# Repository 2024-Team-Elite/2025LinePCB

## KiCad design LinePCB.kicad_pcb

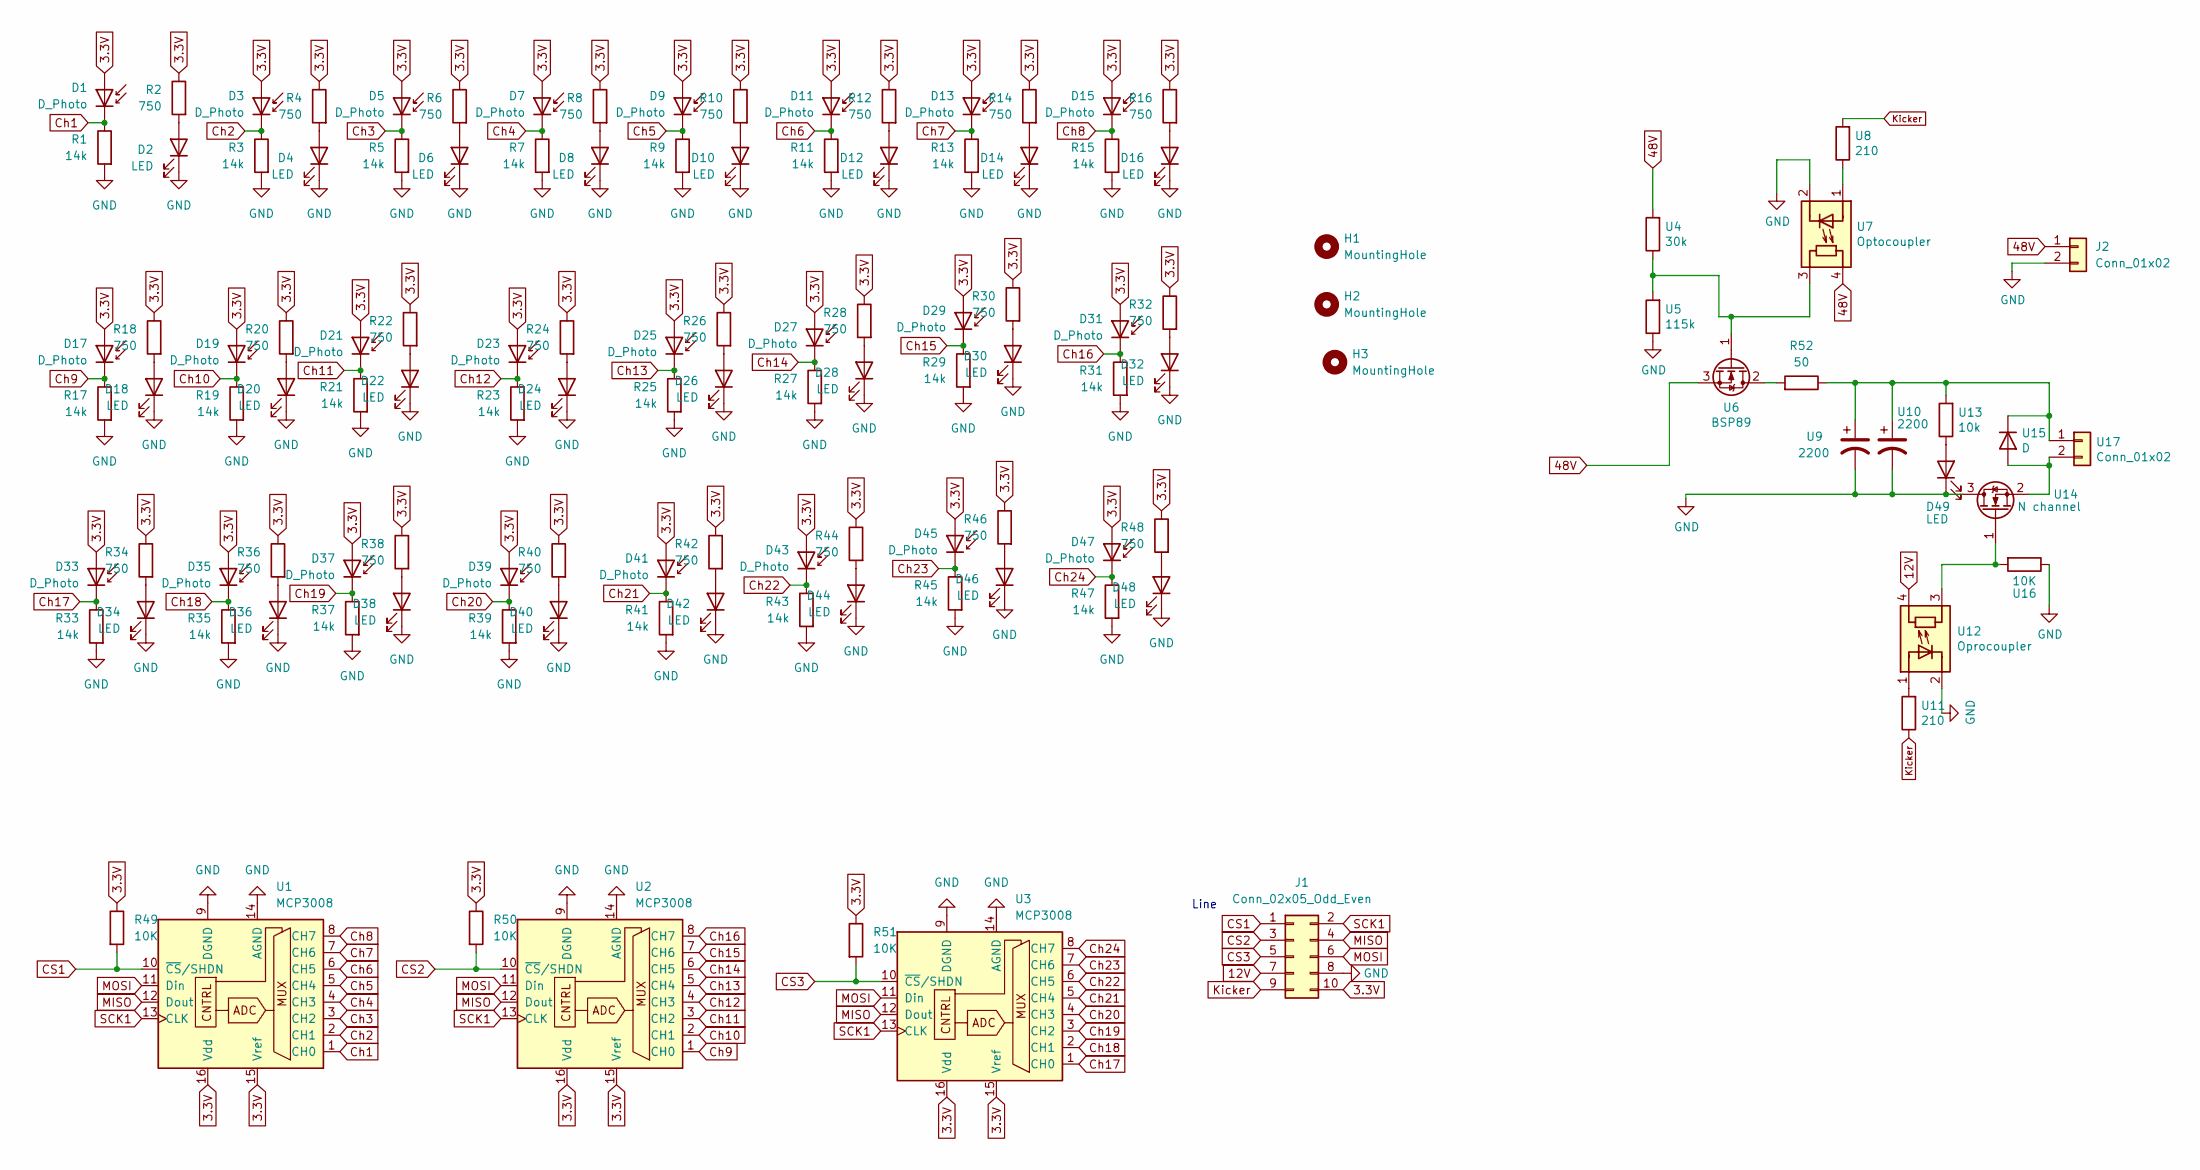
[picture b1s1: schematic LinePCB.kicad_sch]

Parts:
D1, D3, D5, D7, D9, D11, D13, D15, D17, D19, D21, D23, D25, D27, D29, D31, D33, D35, D37, D39, D41, D43, D45, D47: D_Photo; D_0805_2012Metric_Pad1.15x1.40mm_HandSolder
D2, D4, D6, D8, D10, D12, D14, D16, D18, D20, D22, D24, D26, D28, D30, D32, D34, D36, D38, D40, D42, D44, D46, D48, D49: LED; LED_0805_2012Metric_Pad1.15x1.40mm_HandSolder
H1, H2, H3: MountingHole; MountingHole_3.2mm_M3_DIN965_Pad
J1: Conn_02x05_Odd_Even; IDC-Header_2x05_P2.54mm_Vertical
J2: Conn_01x02; JST_XH_B2B-XH-A_1x02_P2.50mm_Vertical
R1, R3, R5, R7, R9, R11, R13, R15, R17, R19, R21, R23, R25, R27, R29, R31, R33, R35, R37, R39, R41, R43, R45, R47: 14k; R_0805_2012Metric_Pad1.20x1.40mm_HandSolder
R2, R4, R6, R8, R10, R12, R14, R16, R18, R20, R22, R24, R26, R28, R30, R32, R34, R36, R38, R40, R42, R44, R46, R48: 750; R_0805_2012Metric_Pad1.20x1.40mm_HandSolder
R49, R50, R51: 10K; R_0805_2012Metric_Pad1.20x1.40mm_HandSolder
R52: 50; TO-220-2_Vertical
U1, U2, U3: MCP3008; SOIC16-N_MC_MCH-L
U4: 30k; R_0805_2012Metric_Pad1.20x1.40mm_HandSolder
U5: 115k; R_0805_2012Metric_Pad1.20x1.40mm_HandSolder
U6: BSP89; TO-220-3_Vertical
U7: Optocoupler; DIP-4_W7.62mm
U8, U11: 210; R_0805_2012Metric_Pad1.20x1.40mm_HandSolder
U9, U10: 2200; CP_Radial_D18.0mm_P7.50mm
U12: Oprocoupler; DIP-4_W7.62mm
U13: 10k; R_0805_2012Metric_Pad1.20x1.40mm_HandSolder
U14: N channel; TO-220-3_Vertical
U15: D; D_5W_P12.70mm_Horizontal
U16: 10K; R_0805_2012Metric_Pad1.20x1.40mm_HandSolder
U17: Conn_01x02; Pads

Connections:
3.3V: D1.2 (A), D3.2 (A), D5.2 (A), D7.2 (A), D9.2 (A), D11.2 (A), D13.2 (A), D15.2 (A), D17.2 (A), D19.2 (A), D21.2 (A), D23.2 (A), D25.2 (A), D27.2 (A), D29.2 (A), D31.2 (A), D33.2 (A), D35.2 (A), D37.2 (A), D39.2 (A), D41.2 (A), D43.2 (A), D45.2 (A), D47.2 (A), J1.10, R2.1, R4.1, R6.1, R8.1, R10.1, R12.1, R14.1, R16.1, R18.1, R20.1, R22.1, R24.1, R26.1, R28.1, R30.1, R32.1, R34.1, R36.1, R38.1, R40.1, R42.1, R44.1, R46.1, R48.1, R49.1, R50.1, R51.1, U1.15 (Vref), U1.16 (Vdd), U2.15 (Vref), U2.16 (Vdd), U3.15 (Vref), U3.16 (Vdd)
12V: J1.7, U12.4 (R)
48V: J2.1, U4.2, U6.3 (S), U7.4 (R)
CS1: J1.1, R49.2, U1.10 (~CS/SHDN)
CS2: J1.3, R50.2, U2.10 (~CS/SHDN)
CS3: J1.5, R51.2, U3.10 (~CS/SHDN)
Ch1: D1.1 (K), R1.1, U1.1 (CH0)
Ch2: D3.1 (K), R3.1, U1.2 (CH1)
Ch3: D5.1 (K), R5.1, U1.3 (CH2)
Ch4: D7.1 (K), R7.1, U1.4 (CH3)
Ch5: D9.1 (K), R9.1, U1.5 (CH4)
Ch6: D11.1 (K), R11.1, U1.6 (CH5)
Ch7: D13.1 (K), R13.1, U1.7 (CH6)
Ch8: D15.1 (K), R15.1, U1.8 (CH7)
Ch9: D17.1 (K), R17.1, U2.1 (CH0)
Ch10: D19.1 (K), R19.1, U2.2 (CH1)
Ch11: D21.1 (K), R21.1, U2.3 (CH2)
Ch12: D23.1 (K), R23.1, U2.4 (CH3)
Ch13: D25.1 (K), R25.1, U2.5 (CH4)
Ch14: D27.1 (K), R27.1, U2.6 (CH5)
Ch15: D29.1 (K), R29.1, U2.7 (CH6)
Ch16: D31.1 (K), R31.1, U2.8 (CH7)
Ch17: D33.1 (K), R33.1, U3.1 (CH0)
Ch18: D35.1 (K), R35.1, U3.2 (CH1)
Ch19: D37.1 (K), R37.1, U3.3 (CH2)
Ch20: D39.1 (K), R39.1, U3.4 (CH3)
Ch21: D41.1 (K), R41.1, U3.5 (CH4)
Ch22: D43.1 (K), R43.1, U3.6 (CH5)
Ch23: D45.1 (K), R45.1, U3.7 (CH6)
Ch24: D47.1 (K), R47.1, U3.8 (CH7)
GND: D2.1 (K), D4.1 (K), D6.1 (K), D8.1 (K), D10.1 (K), D12.1 (K), D14.1 (K), D16.1 (K), D18.1 (K), D20.1 (K), D22.1 (K), D24.1 (K), D26.1 (K), D28.1 (K), D30.1 (K), D32.1 (K), D34.1 (K), D36.1 (K), D38.1 (K), D40.1 (K), D42.1 (K), D44.1 (K), D46.1 (K), D48.1 (K), D49.1 (K), J1.8, J2.2, R1.2, R3.2, R5.2, R7.2, R9.2, R11.2, R13.2, R15.2, R17.2, R19.2, R21.2, R23.2, R25.2, R27.2, R29.2, R31.2, R33.2, R35.2, R37.2, R39.2, R41.2, R43.2, R45.2, R47.2, U1.9 (DGND), U1.14 (AGND), U2.9 (DGND), U2.14 (AGND), U3.9 (DGND), U3.14 (AGND), U5.1, U7.2 (K), U9.2, U10.2, U12.2 (K), U14.3 (D), U16.1
Kicker: J1.9, U8.2, U11.1
MISO: J1.4, U1.12 (Dout), U2.12 (Dout), U3.12 (Dout)
MOSI: J1.6, U1.11 (Din), U2.11 (Din), U3.11 (Din)
unnamed: D2.2 (A), R2.2
unnamed: D4.2 (A), R4.2
unnamed: D6.2 (A), R6.2
unnamed: D8.2 (A), R8.2
unnamed: D10.2 (A), R10.2
unnamed: D12.2 (A), R12.2
unnamed: D14.2 (A), R14.2
unnamed: D16.2 (A), R16.2
unnamed: D18.2 (A), R18.2
unnamed: D20.2 (A), R20.2
unnamed: D22.2 (A), R22.2
unnamed: D24.2 (A), R24.2
unnamed: D26.2 (A), R26.2
unnamed: D28.2 (A), R28.2
unnamed: D30.2 (A), R30.2
unnamed: D32.2 (A), R32.2
unnamed: D34.2 (A), R34.2
unnamed: D36.2 (A), R36.2
unnamed: D38.2 (A), R38.2
unnamed: D40.2 (A), R40.2
unnamed: D42.2 (A), R42.2
unnamed: D44.2 (A), R44.2
unnamed: D46.2 (A), R46.2
unnamed: D48.2 (A), R48.2
unnamed: D49.2 (A), U13.1
unnamed: R52.2, U6.2 (D)
unnamed: U4.1, U5.2, U6.1 (G), U7.3 (R)
unnamed: U7.1 (A), U8.1
unnamed: U11.2, U12.1 (A)
unnamed: U12.3 (R), U14.1 (G), U16.2
unnamed: U14.2 (S), U15.2 (A), U17.2
unnamed: R52.1, U9.1, U10.1, U13.2, U15.1 (K), U17.1
SCK1: J1.2, U1.13 (CLK), U2.13 (CLK), U3.13 (CLK)

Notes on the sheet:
Line

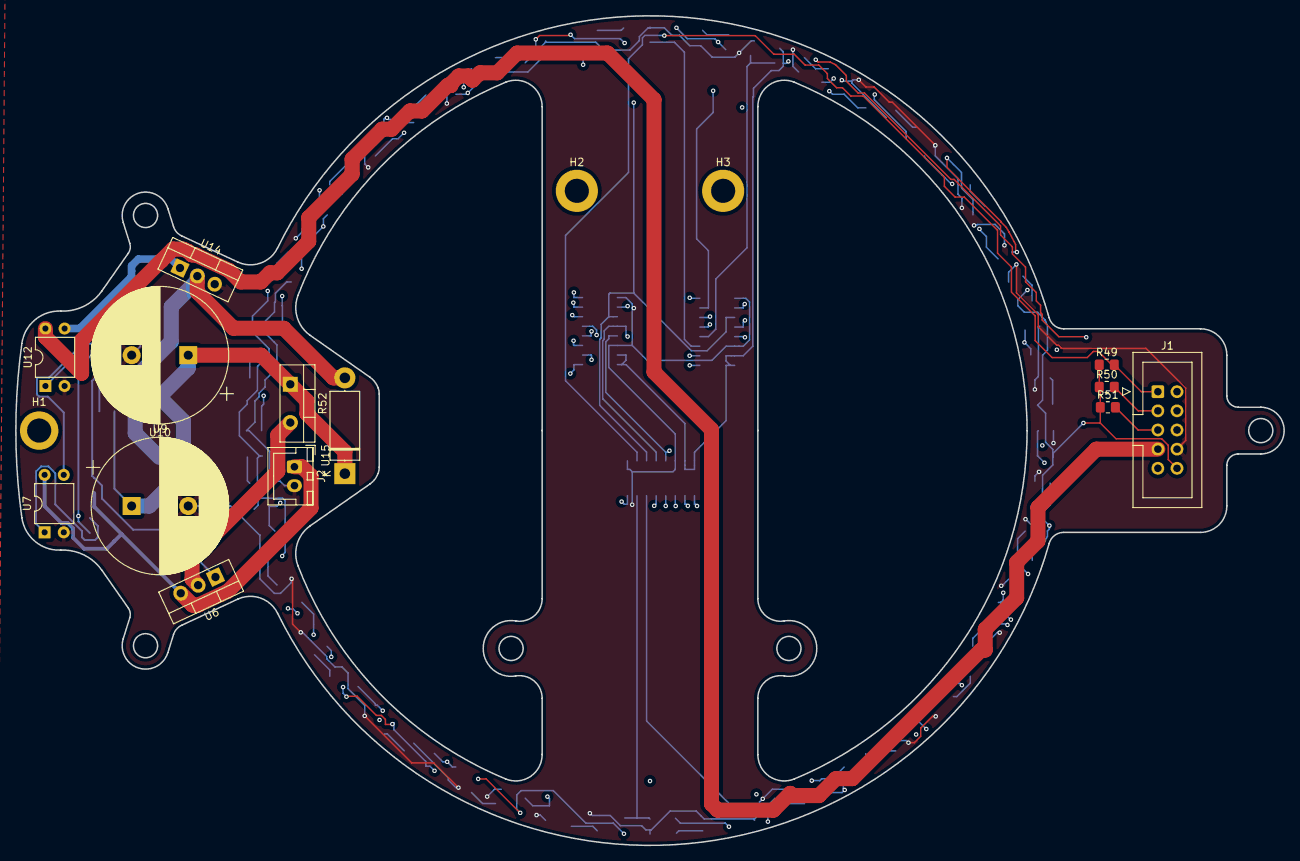
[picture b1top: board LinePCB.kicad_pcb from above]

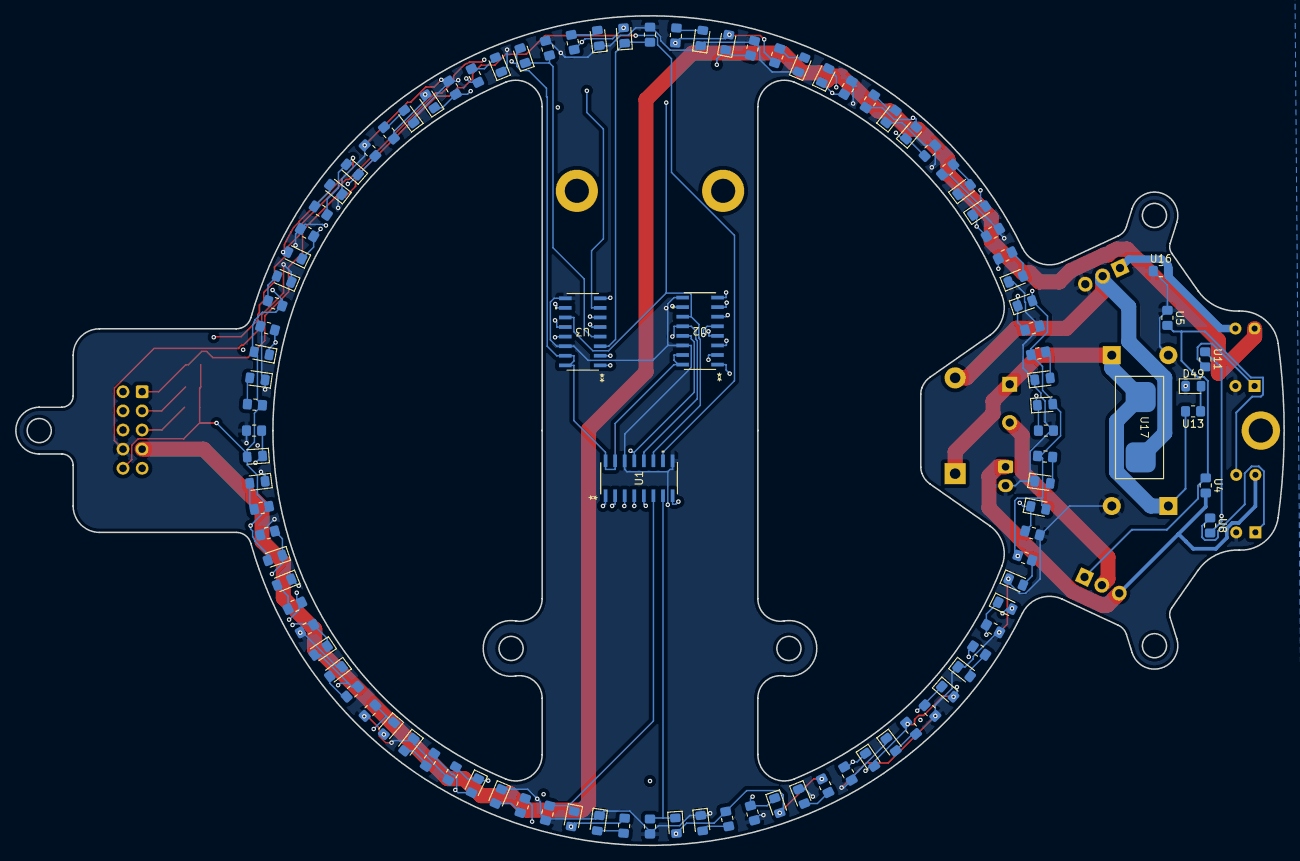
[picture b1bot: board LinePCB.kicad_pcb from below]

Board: 4 copper layers, 168.2 x 110.0 mm, 123 parts (107 on the bottom side), 67 nets.

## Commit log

2024-11-10 Finished Schematic
2024-11-11 Finished Placement
2024-11-12 Finished PCB
2024-11-15 Fixed Main 12V trace
2024-11-15 fixed all 120 fucking pcb errors, its 12:30am and i have school tomorrow
2024-11-15 made gerbers
